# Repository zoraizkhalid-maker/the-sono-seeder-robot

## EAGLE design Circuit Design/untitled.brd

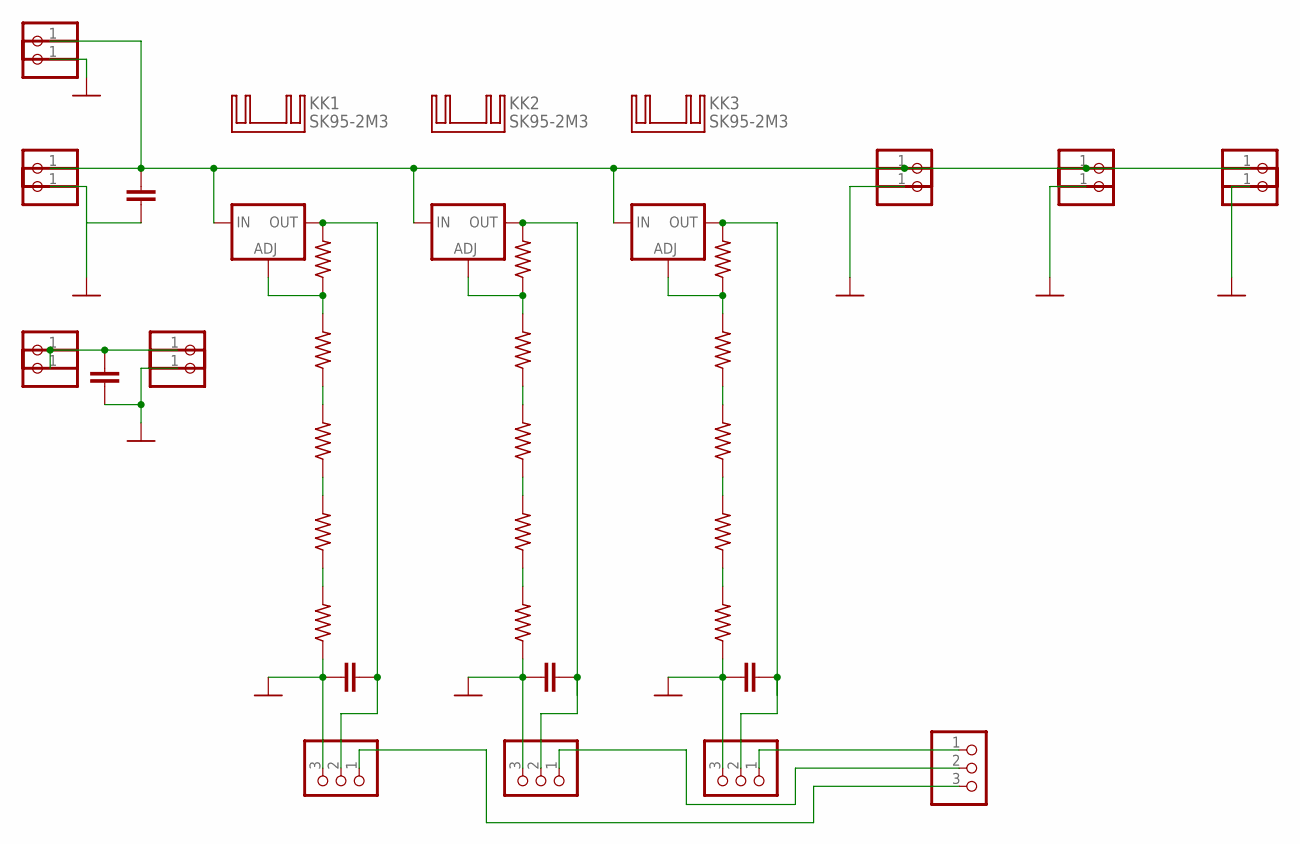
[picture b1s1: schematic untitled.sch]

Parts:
5V, 5V+, 5V-, 5VV: PINHD-1X1; 1X01
BATTERY+: PINHD-1X1; 1X01
BATTERY-: PINHD-1X1; 1X01
C1, C2, C3, C4, C5: C-EU025-050X050; C025-050X050
D1+, D1-, D2+, D2-, D3+, D3-: PINHD-1X1; 1X01
IC4, IC5, IC6: LM317TS; 317TS
JP1, JP2, JP3, JP6: PINHD-1X3; 1X03
KK1, KK2, KK3: SK95-2M3
R1, R2, R5, R6, R7, R8, R9, R10, R11, R12, R13, R14, R15, R16, R17: R-US_0207/10; 0207/10
SOLAR+: PINHD-1X1; 1X01
SOLAR-: PINHD-1X1; 1X01

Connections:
GND: 5V-.1, BATTERY-.1, C1.1, C2.1, C3.1, C4.2, C5.2, D1-.1, D2-.1, D3-.1, JP1.3, JP2.3, JP3.3, R8.1, R13.1, R17.1, SOLAR-.1
unnamed: C1.2, IC4.2 (OUT), JP2.2, R10.2
unnamed: IC4.1 (ADJ), R9.2, R10.1
unnamed: R9.1, R11.2
unnamed: R11.1, R12.2
unnamed: R12.1, R13.2
unnamed: R1.1, R6.2
unnamed: R6.1, R7.2
unnamed: R7.1, R8.2
unnamed: C3.2, IC5.2 (OUT), JP3.2, R5.2
unnamed: IC5.1 (ADJ), R5.1, R14.2
unnamed: R14.1, R15.2
unnamed: R15.1, R16.2
unnamed: R16.1, R17.2
unnamed: BATTERY+.1, C4.1, D1+.1, D2+.1, D3+.1, IC4.3 (IN), IC5.3 (IN), IC6.3 (IN), SOLAR+.1
unnamed: JP2.1, JP6.3
unnamed: JP1.1, JP6.2
unnamed: JP3.1, JP6.1
unnamed: 5V.1, 5V+.1, 5VV.1, C5.1
unnamed: C2.2, IC6.2 (OUT), JP1.2, R2.2
unnamed: IC6.1 (ADJ), R1.2, R2.1

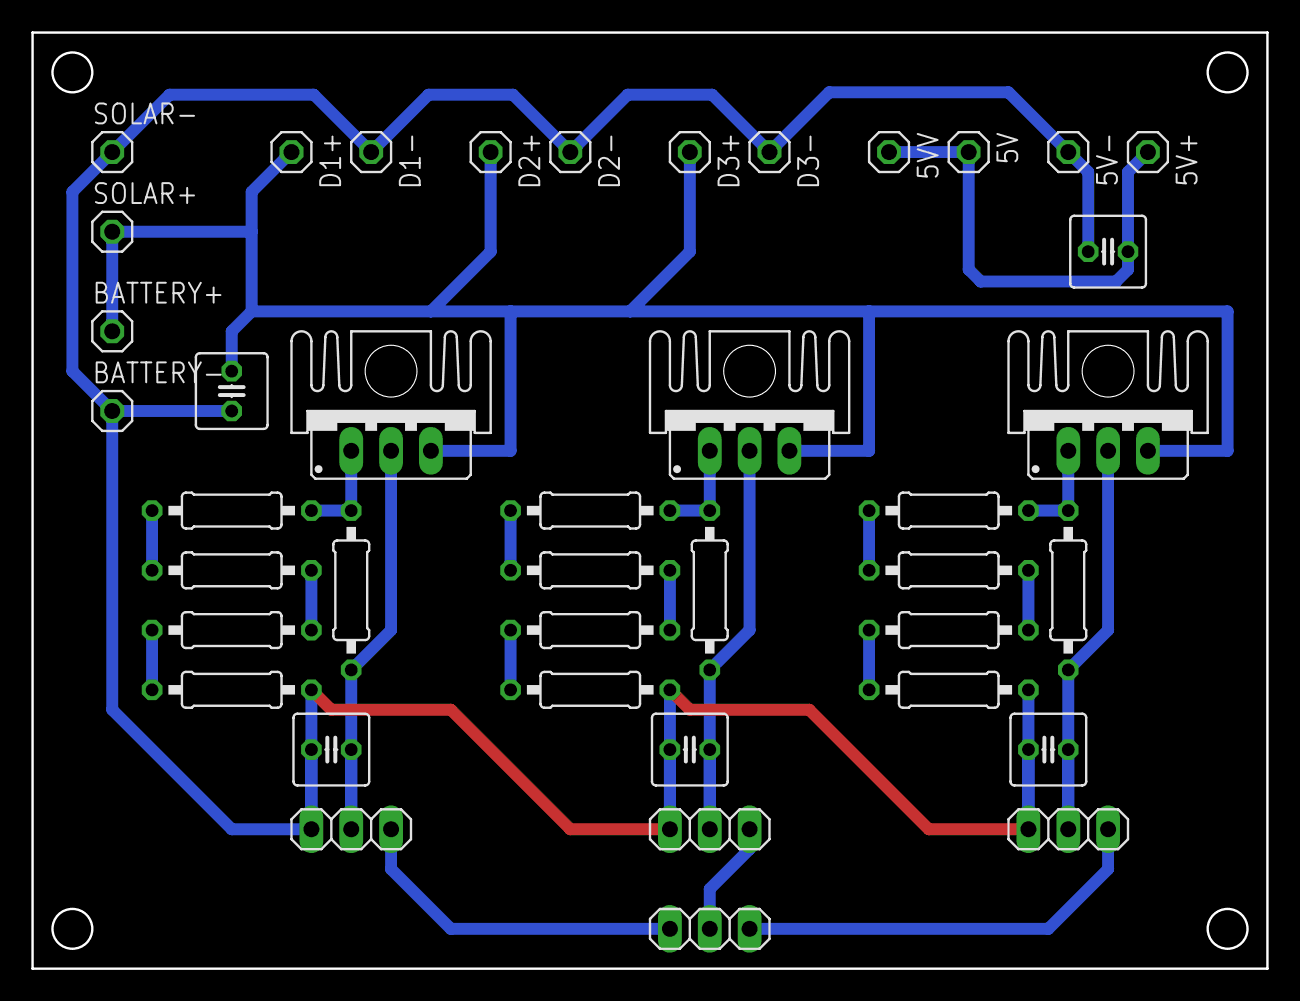
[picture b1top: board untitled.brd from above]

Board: 2 copper layers, 78.7 x 59.7 mm, 44 parts (0 on the bottom side), 21 nets.
